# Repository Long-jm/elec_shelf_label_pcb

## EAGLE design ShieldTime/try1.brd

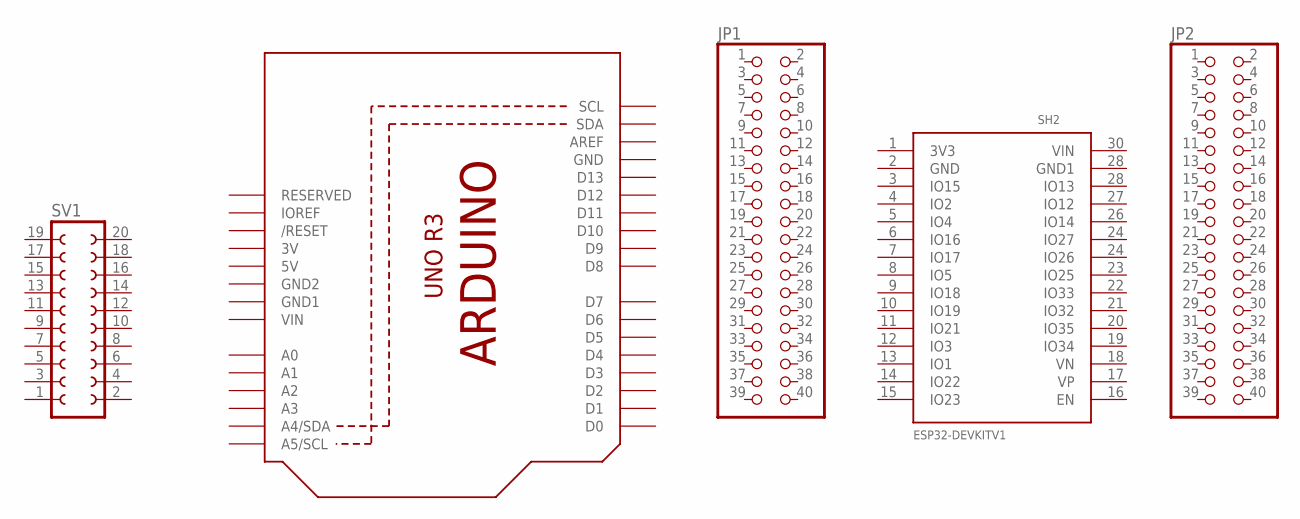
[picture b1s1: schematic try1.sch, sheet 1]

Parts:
JP1, JP2: PINHD-2X20; 2X20
SH1: ARDUINOR3-BPLACE
SH2: ESP32DEVKITV1; ESP32-DEVKITV1
SV1: FE10-2

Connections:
3V: SH1.3V
5V: SH1.5V
GND: SH1.GND; also elsewhere on the board
GND1: SH1.GND1
GND2: SH1.GND2
VIN: SH1.VIN

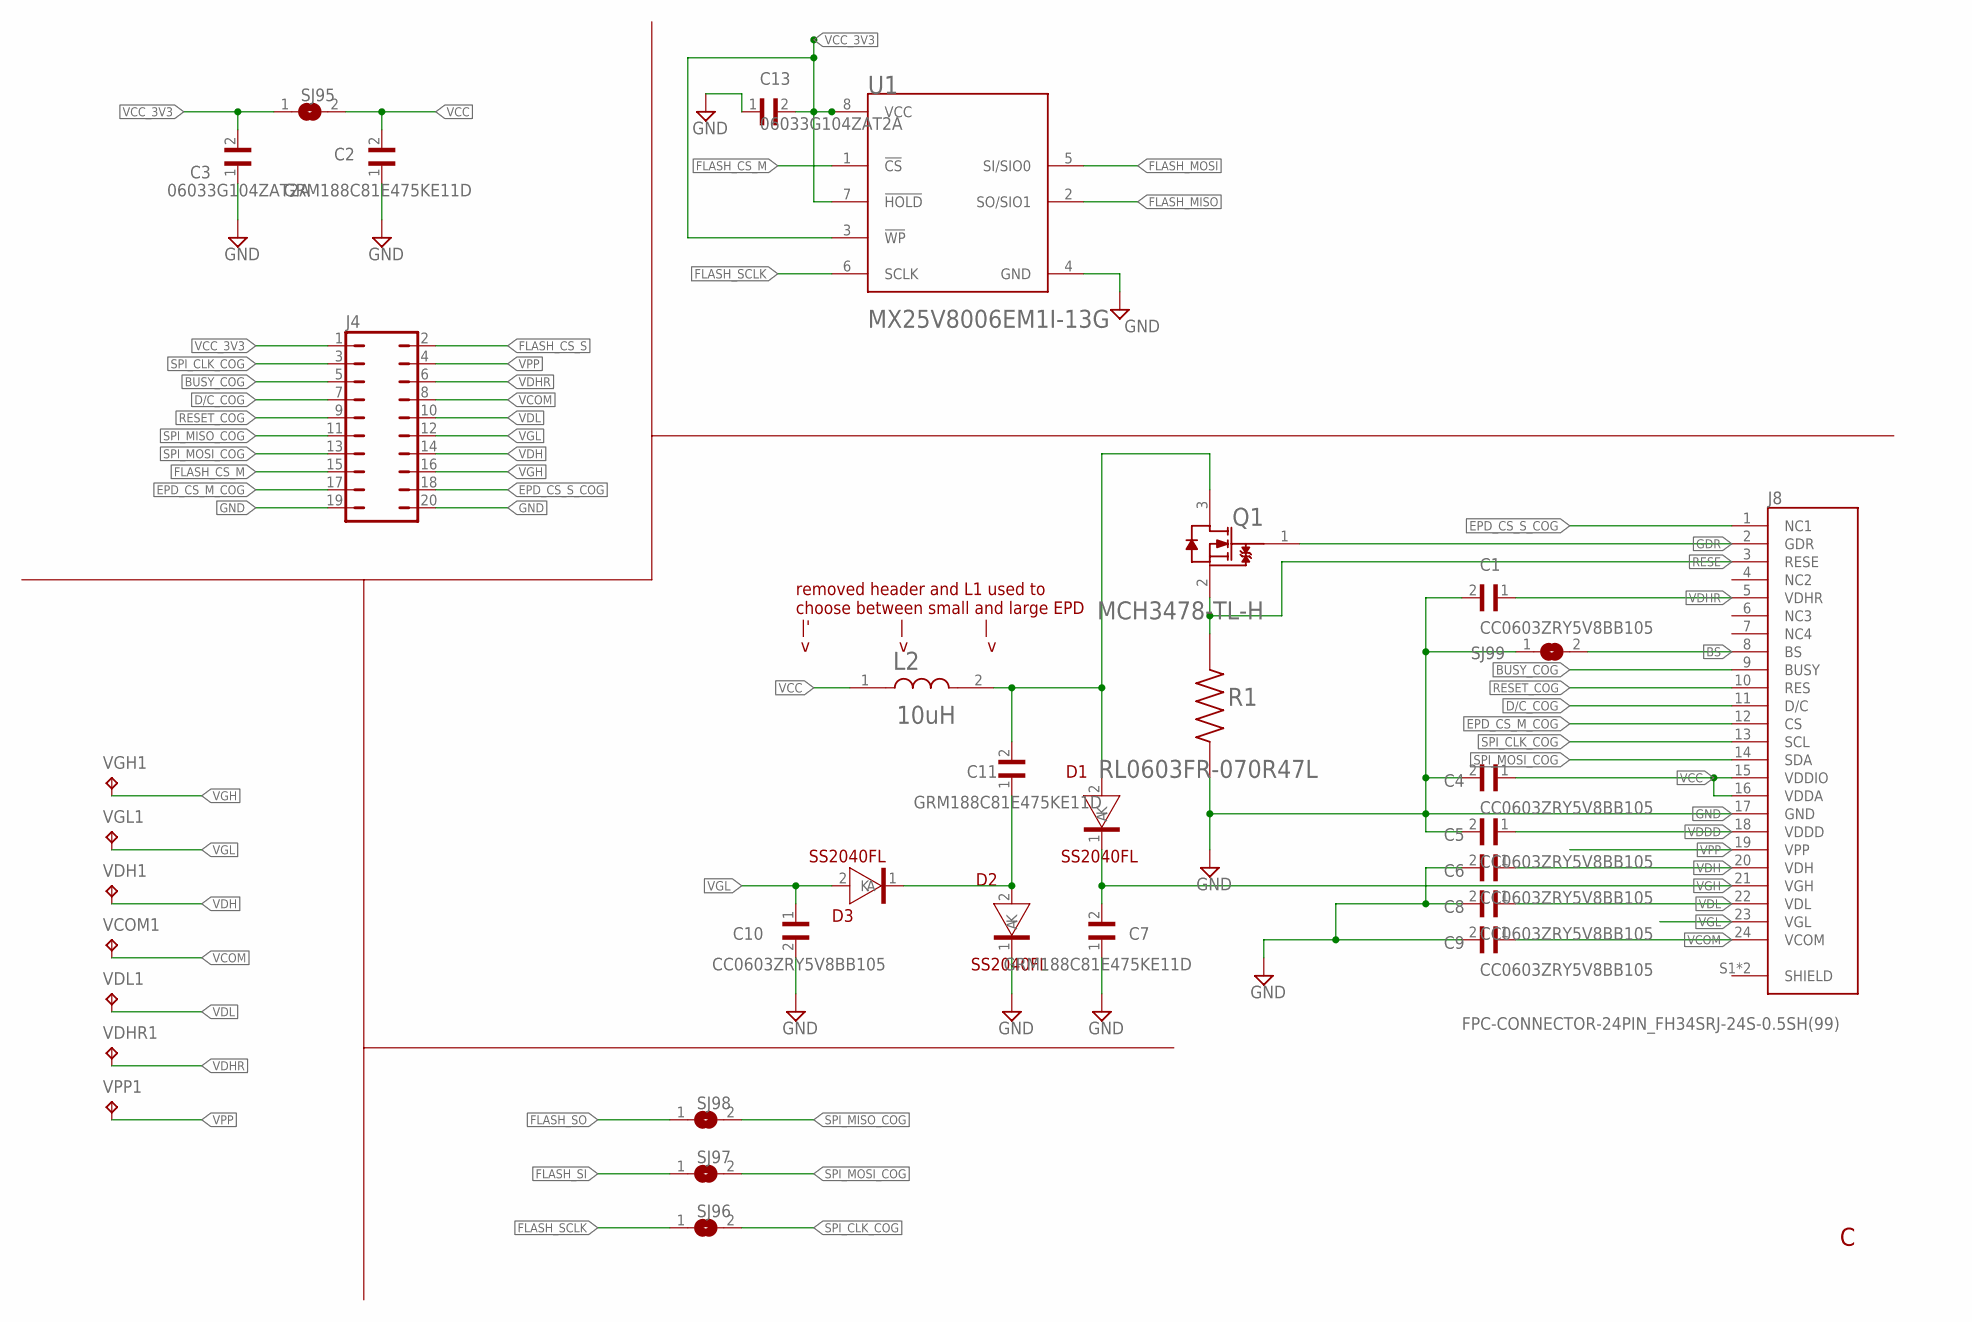
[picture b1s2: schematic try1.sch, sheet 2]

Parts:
C1, C4, C5, C6, C8, C9, C10: CC0603ZRY5V8BB105; CAPC1608X90
C2, C7, C11: GRM188C81E475KE11D; CAPC1608X100N
C3, C13: 06033G104ZAT2A; CAPC1608X90N
D1, D2, D3: SS2040FL; SOD-123FL
J4: JP10Q
J8: FPC-CONNECTOR-24PIN_FH34SRJ-24S-0.5SH(99); FPC-CONNECTOR-24PIN_HRS_FH34SRJ-24S-0.5SH(99)
L2: MURATA_LQH3NPZ100MMELMURATA_LQH3NPZ100MMEL_0_0; MURATA_LQH3NPZ100MMEL_0
Q1: ON_SEMICONDUCTOR_MCH3478-TL-HON_SEMICONDUCTOR_MCH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; ON_SEMICONDUCTOR_MCH3478-TL-H_0
R1: RL0603FR-070R47L; RESC1608X55N
SJ95, SJ96, SJ97, SJ98, SJ99: SJW
U1: MACRONIX_MX25V8006EM1I-13GMACRONIX_MX25V8006EM1I-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; MACRONIX_MX25V8006EM1I-13G_0
VCOM1: TPB1,27; B1,27
VDH1: TPB1,27; B1,27
VDHR1: TPB1,27; B1,27
VDL1: TPB1,27; B1,27
VGH1: TPB1,27; B1,27
VGL1: TPB1,27; B1,27
VPP1: TPB1,27; B1,27

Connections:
BS: J8.8 (BS), SJ99.2
BUSY_COG: J4.5, J8.9 (BUSY)
D/C_COG: J4.7, J8.11 (D/C)
EPD_CS_M_COG: J4.17, J8.12 (CS)
EPD_CS_S_COG: J4.18, J8.1 (NC1)
FLASH_CS_M: J4.15, U1.1 (!CS!)
FLASH_CS_S: J4.2
FLASH_MISO: U1.2 (SO/SIO1)
FLASH_MOSI: U1.5 (SI/SIO0)
FLASH_SCLK: SJ96.1, U1.6 (SCLK)
FLASH_SI: SJ97.1
FLASH_SO: SJ98.1
GDR: J8.2 (GDR), Q1.1 (G)
GND: C1.2, C2.1, C3.1, C4.2, C5.2, C6.2, C7.1, C8.2, C9.2, C10.2, C13.1, D2.1 (K), J4.19, J4.20, J8.17 (GND), R1.1, SJ99.1, U1.4 (GND); also elsewhere on the board
unnamed: C11.2, D1.2 (A), L2.2, Q1.3 (D)
unnamed: C11.1, D2.2 (A), D3.1 (K)
RESE: J8.3 (RESE), Q1.2 (S), R1.2
RESET_COG: J4.9, J8.10 (RES)
SPI_CLK_COG: J4.3, J8.13 (SCL), SJ96.2
SPI_MISO_COG: J4.11, SJ98.2
SPI_MOSI_COG: J4.13, J8.14 (SDA), SJ97.2
VCC: C2.2, C4.1, J8.15 (VDDIO), J8.16 (VDDA), L2.1, SJ95.2
VCC_3V3: C3.2, C13.2, J4.1, SJ95.1, U1.3 (!WP!), U1.7 (!HOLD!), U1.8 (VCC)
VCOM: C9.1, J4.8, J8.24 (VCOM), VCOM1.TP
VDDD: C5.1, J8.18 (VDDD)
VDH: C6.1, J4.14, J8.20 (VDH), VDH1.TP
VDHR: C1.1, J4.6, J8.5 (VDHR), VDHR1.TP
VDL: C8.1, J4.10, J8.22 (VDL), VDL1.TP
VGH: C7.2, D1.1 (K), J4.16, J8.21 (VGH), VGH1.TP
VGL: C10.1, D3.2 (A), J4.12, J8.23 (VGL), VGL1.TP
VPP: J4.4, J8.19 (VPP), VPP1.TP

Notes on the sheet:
removed header and L1 used to choose between small and large EPD |' | | v v v

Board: 2 copper layers, 38 parts (19 on the bottom side), 26 nets, no tracks yet.

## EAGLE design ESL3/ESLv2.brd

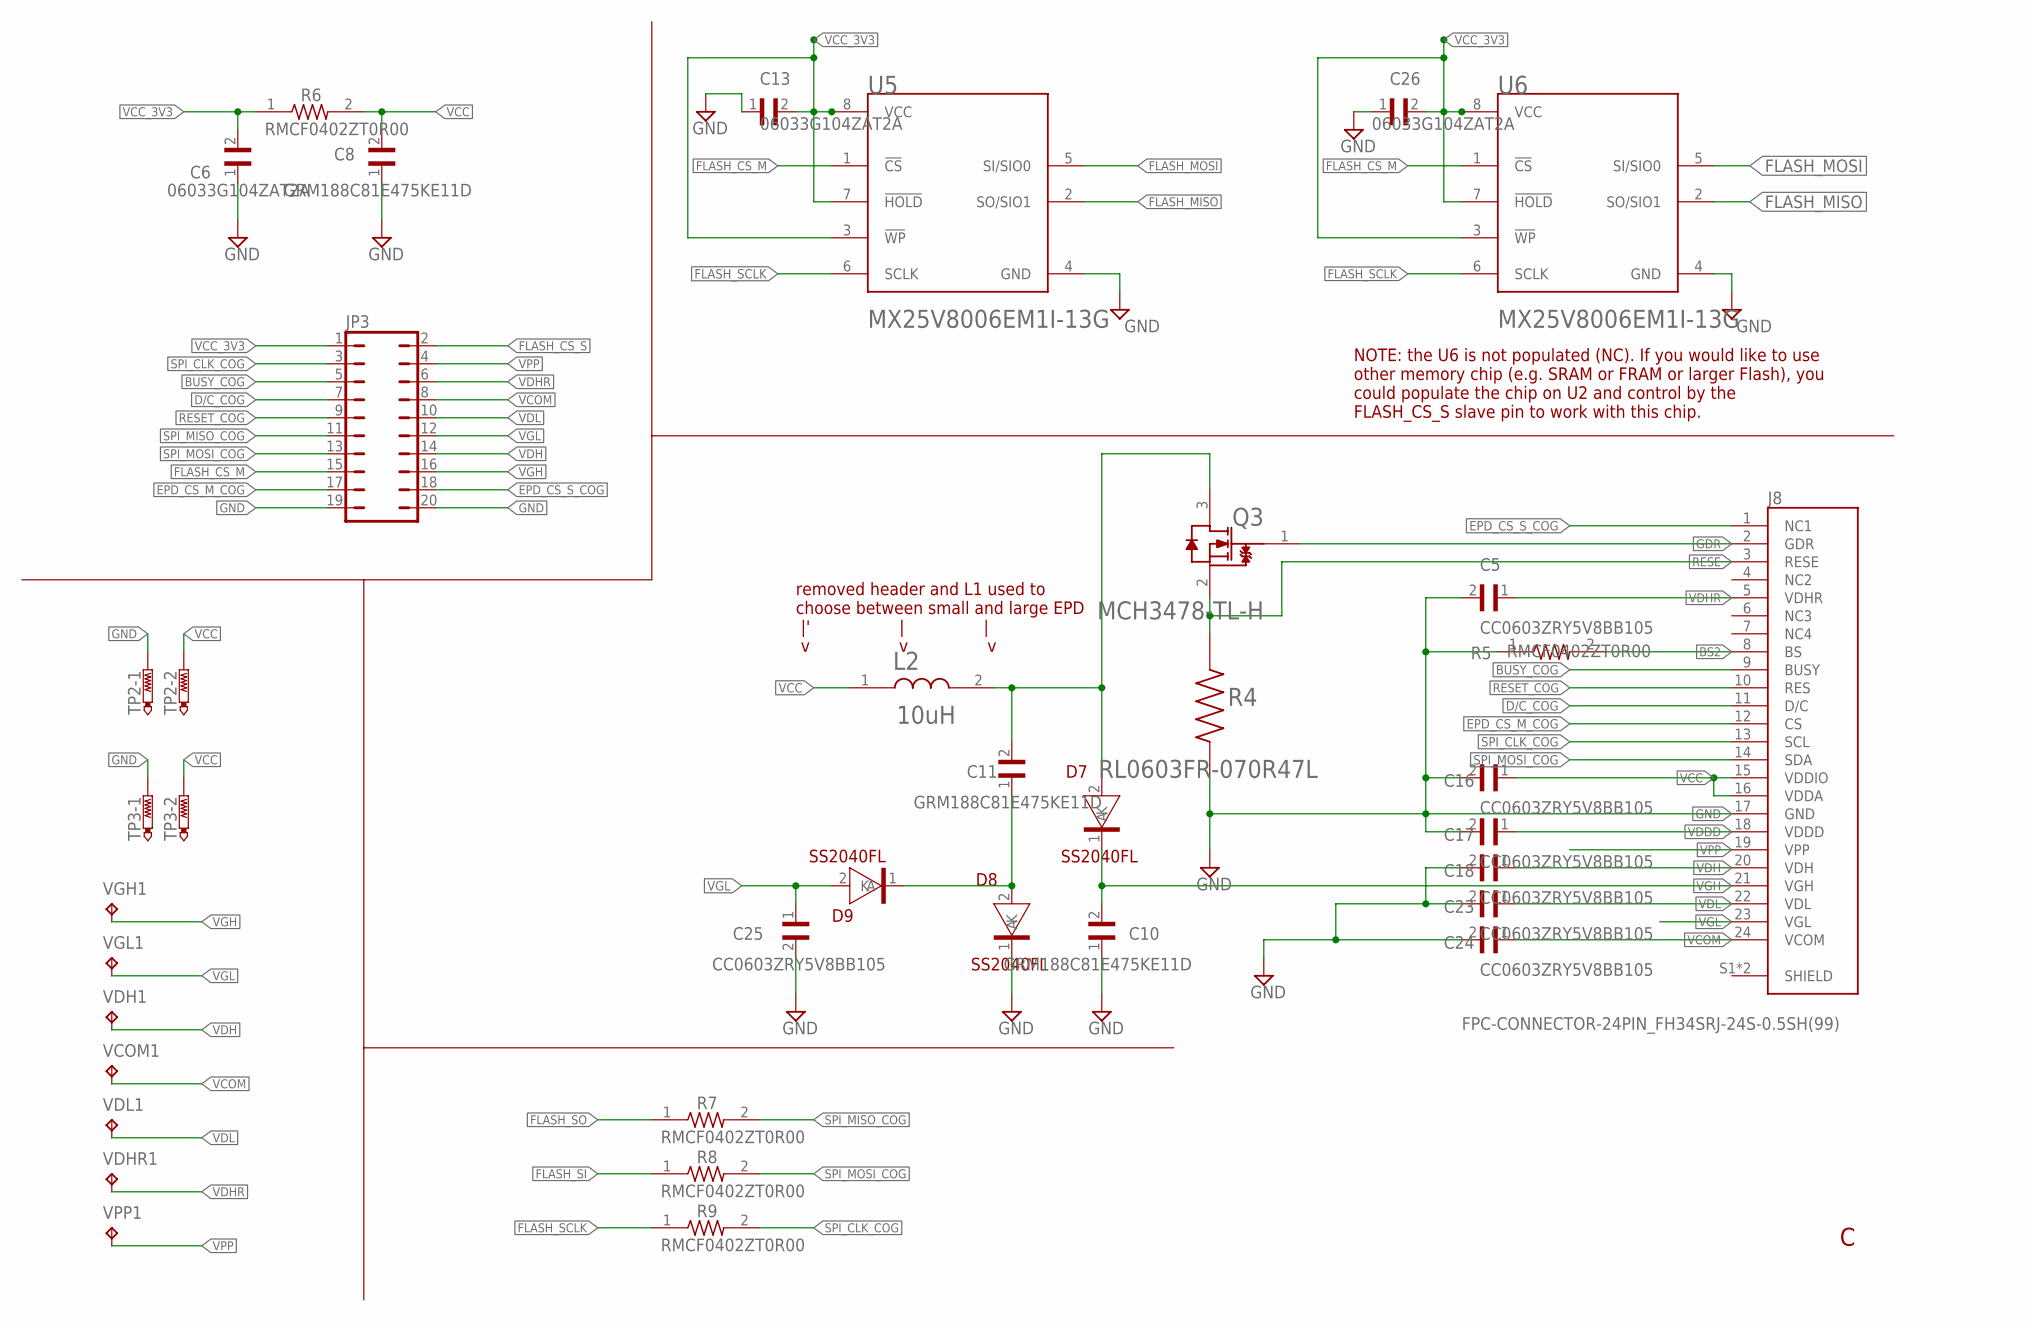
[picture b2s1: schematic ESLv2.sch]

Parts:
C5, C16, C17, C18, C23, C24, C25: CC0603ZRY5V8BB105; CAPC1608X90
C6, C13, C26: 06033G104ZAT2A; CAPC1608X90N
C8, C10, C11: GRM188C81E475KE11D; CAPC1608X100N
D7, D8, D9: SS2040FL; SOD-123FL
J8: FPC-CONNECTOR-24PIN_FH34SRJ-24S-0.5SH(99); FPC-CONNECTOR-24PIN_HRS_FH34SRJ-24S-0.5SH(99)
JP3: JP10Q
L2: MURATA_LQH3NPZ100MMELMURATA_LQH3NPZ100MMEL_0_0; MURATA_LQH3NPZ100MMEL_0
Q3: ON_SEMICONDUCTOR_MCH3478-TL-HON_SEMICONDUCTOR_MCH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; ON_SEMICONDUCTOR_MCH3478-TL-H_0
R4: RL0603FR-070R47L; RESC1608X55N
R5, R6, R7, R8, R9: RMCF0402ZT0R00; RESC1005X40
TP2, TP3: PTR2; P2-38-17
U5, U6: MACRONIX_MX25V8006EM1I-13GMACRONIX_MX25V8006EM1I-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; MACRONIX_MX25V8006EM1I-13G_0
VCOM1: TPB1,27; B1,27
VDH1: TPB1,27; B1,27
VDHR1: TPB1,27; B1,27
VDL1: TPB1,27; B1,27
VGH1: TPB1,27; B1,27
VGL1: TPB1,27; B1,27
VPP1: TPB1,27; B1,27

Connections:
BS2: C6.1, C8.1, C10.1, C13.1, C25.2, C26.1, D8.1 (K), J8.8 (BS), R5.2, U5.4 (GND), U6.4 (GND)
BUSY_COG: J8.9 (BUSY), JP3.5
D/C_COG: J8.11 (D/C), JP3.7
EPD_CS_M_COG: J8.12 (CS), JP3.17
EPD_CS_S_COG: J8.1 (NC1), JP3.18
FLASH_CS_M: JP3.15, U5.1 (!CS!), U6.1 (!CS!)
FLASH_CS_S: JP3.2
FLASH_MISO: U5.2 (SO/SIO1), U6.2 (SO/SIO1)
FLASH_MOSI: U5.5 (SI/SIO0), U6.5 (SI/SIO0)
FLASH_SCLK: R9.1, U5.6 (SCLK), U6.6 (SCLK)
FLASH_SI: R8.1
FLASH_SO: R7.1
GDR: J8.2 (GDR), Q3.1 (G)
GND: C5.2, C16.2, C17.2, C18.2, C23.2, C24.2, J8.17 (GND), JP3.19, JP3.20, R4.1, R5.1, TP2.TP-1, TP3.TP-1
unnamed: C11.2, D7.2 (A), L2.2, Q3.3 (D)
unnamed: C11.1, D8.2 (A), D9.1 (K)
RESE: J8.3 (RESE), Q3.2 (S), R4.2
RESET_COG: J8.10 (RES), JP3.9
SPI_CLK_COG: J8.13 (SCL), JP3.3, R9.2
SPI_MISO_COG: JP3.11, R7.2
SPI_MOSI_COG: J8.14 (SDA), JP3.13, R8.2
VCC: C8.2, C16.1, J8.15 (VDDIO), J8.16 (VDDA), L2.1, R6.2, TP2.TP-2, TP3.TP-2
VCC_3V3: C6.2, C13.2, C26.2, JP3.1, R6.1, U5.3 (!WP!), U5.7 (!HOLD!), U5.8 (VCC), U6.3 (!WP!), U6.7 (!HOLD!), U6.8 (VCC)
VCOM: C24.1, J8.24 (VCOM), JP3.8, VCOM1.TP
VDDD: C17.1, J8.18 (VDDD)
VDH: C18.1, J8.20 (VDH), JP3.14, VDH1.TP
VDHR: C5.1, J8.5 (VDHR), JP3.6, VDHR1.TP
VDL: C23.1, J8.22 (VDL), JP3.10, VDL1.TP
VGH: C10.2, D7.1 (K), J8.21 (VGH), JP3.16, VGH1.TP
VGL: C25.1, D9.2 (A), J8.23 (VGL), JP3.12, VGL1.TP
VPP: J8.19 (VPP), JP3.4, VPP1.TP

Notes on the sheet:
removed header and L1 used to choose between small and large EPD |' | | v v v
NOTE: the U6 is not populated (NC). If you would like to use other memory chip (e.g. SRAM or FRAM or larger Flash), you could populate the chip on U2 and control by the FLASH_CS_S slave pin to work with this chip.

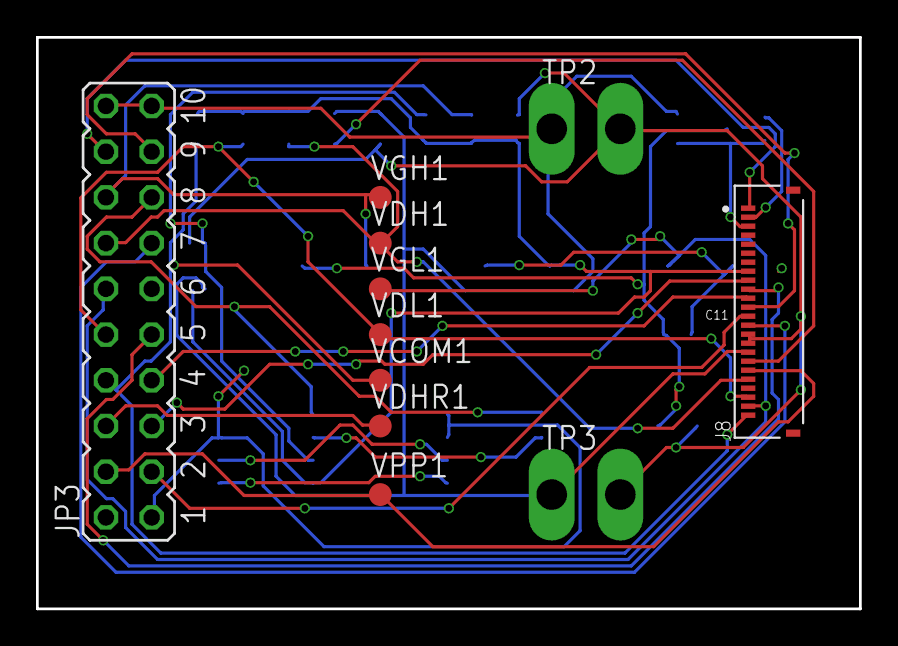
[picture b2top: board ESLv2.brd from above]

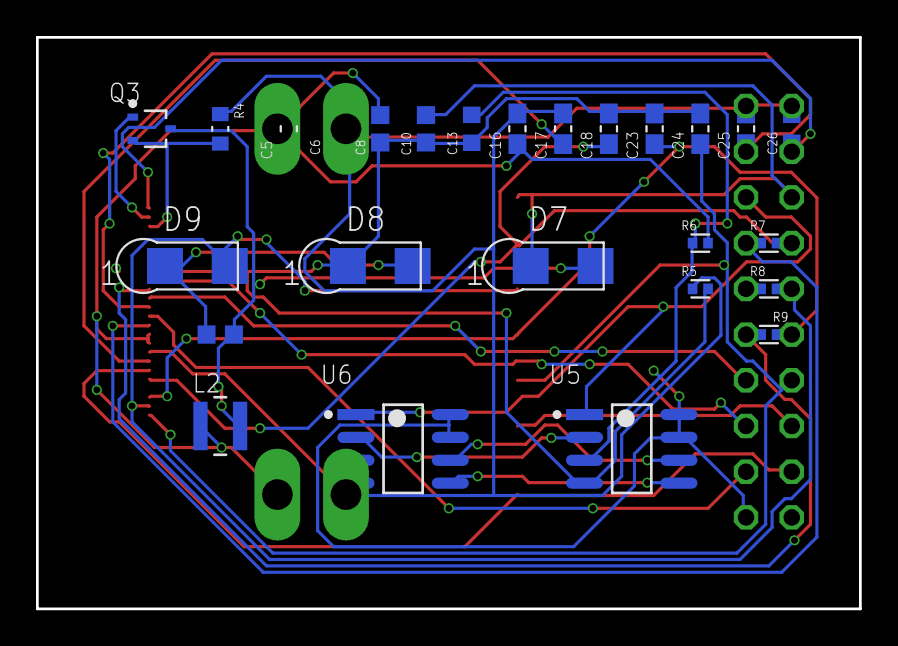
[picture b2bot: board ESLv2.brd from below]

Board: 2 copper layers, 45.7 x 31.8 mm, 37 parts (26 on the bottom side), 28 nets.
